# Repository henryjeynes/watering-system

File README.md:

# watering-system

**This project is on hold for the moment. The boards, schematics, and code in this repo are not guaranteed to work. Please let me know if you have any questions about the project.**

Automatic watering system based on ATmegaxx8 microcontrollers.

Using the code or boards is not currently recommended for long-term use.

TODO:
(items in **bold** are scheduled for the next release. Items which have been dealt with are ~~struck through~~.)
  * Add EEPROM-stored settings, which can be changed over the serial port
  * Add sleep code for lower power consumption
  * ~~Add individual watering. The code currently uses one pump for both plants~~
  * Replace linear regulator with switching
  * Add optional float switch for water tank
  * Add optional voltage sensing for batteries (with settings for various chemistries)

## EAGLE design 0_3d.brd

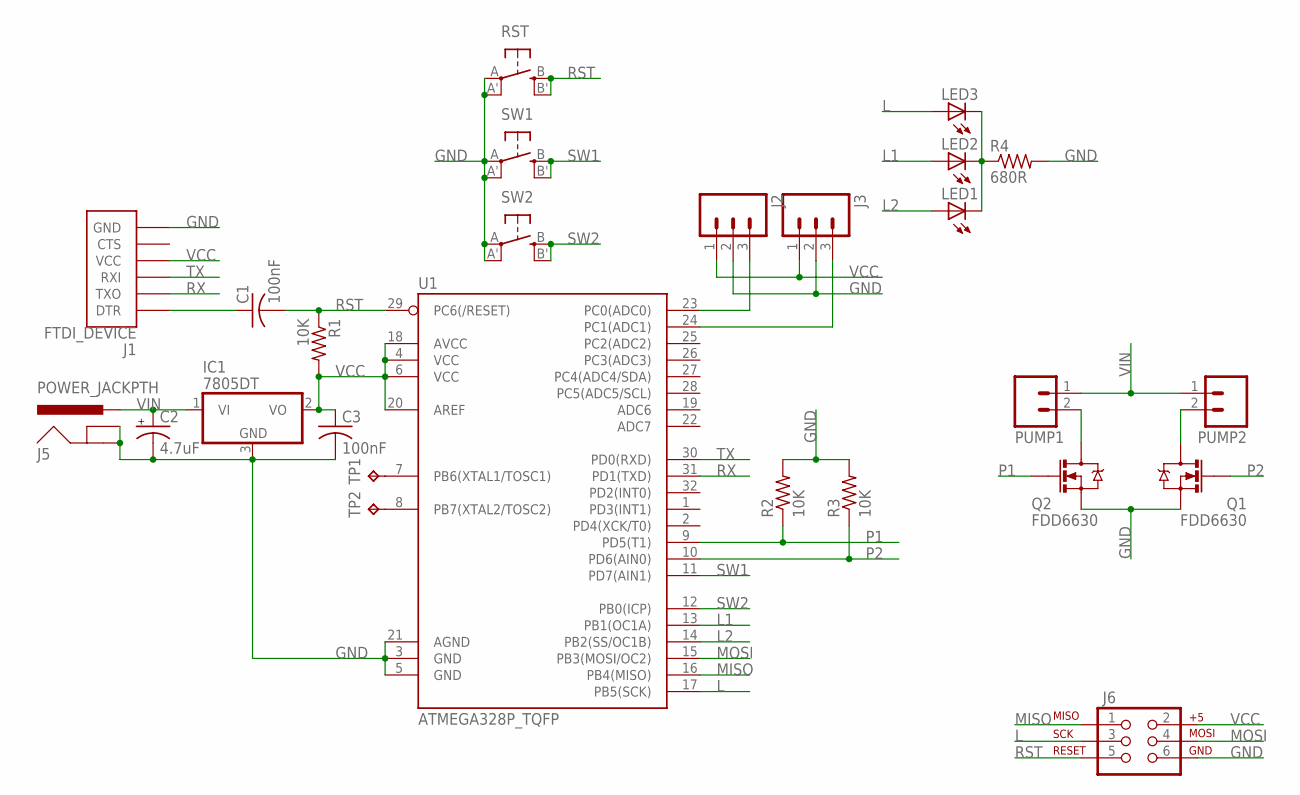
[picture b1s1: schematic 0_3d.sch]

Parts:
C1, C3: 100nF; C1206K
C2: 4.7uF; 153CLV-0405
IC1: 7805DT; TO252
J1: FTDI_DEVICE; FTDI_DEVICE_SIDE
J2, J3: M03PTH; 1X03
J5: POWER_JACKPTH; POWER_JACK_PTH
J6: AVR_SPI_PRG_6PTH; 2X3
LED1, LED2, LED3: LED3MM
PUMP1, PUMP2: M02PTH; 1X02
Q1, Q2: FDD6630; D-PAK_TO252AA
R1, R2, R3: 10K; M0805
R4: 680R; M0805
RST: SPST_TACT-EVQQ2; EVQ-Q2
SW1, SW2: SPST_TACT-EVQQ2; EVQ-Q2
TP1, TP2: TPTP15SQ; TP15SQ
U1: ATMEGA328P_TQFP; TQFP32-08

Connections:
GND: C2.-, C3.2, IC1.3 (GND), J1.P$6 (GND), J2.2, J3.2, J5.GND, J5.GNDBREAK, J6.6, Q1.3 (S), Q2.3 (S), R2.2, R3.2, R4.2, RST.A, RST.A' (P1), SW1.A, SW1.A' (P1), SW2.A, SW2.A' (P1), U1.3 (GND), U1.5 (GND), U1.21 (AGND)
L: J6.3, LED3.A, U1.17 (PB5(SCK))
L1: LED2.A, U1.13 (PB1(OC1A))
L2: LED1.A, U1.14 (PB2(SS/OC1B))
MISO: J6.1, U1.16 (PB4(MISO))
MOSI: J6.4, U1.15 (PB3(MOSI/OC2))
unnamed: LED1.K (C), LED2.K (C), LED3.K (C), R4.1
unnamed: TP1.TP, U1.7 (PB6(XTAL1/TOSC1))
unnamed: PUMP2.2, Q1.2 (D)
unnamed: C1.1, J1.P$1 (DTR)
unnamed: TP2.TP, U1.8 (PB7(XTAL2/TOSC2))
unnamed: PUMP1.2, Q2.2 (D)
unnamed: J2.3, U1.23 (PC0(ADC0))
unnamed: J3.3, U1.24 (PC1(ADC1))
P1: Q2.1 (G), R2.1, U1.9 (PD5(T1))
P2: Q1.1 (G), R3.1, U1.10 (PD6(AIN0))
RST: C1.2, J6.5, R1.1, RST.B (S), RST.B' (S1), U1.29 (PC6(/RESET))
RX: J1.P$2 (TXO), U1.31 (PD1(TXD))
SW1: SW1.B (S), SW1.B' (S1), U1.11 (PD7(AIN1))
SW2: SW2.B (S), SW2.B' (S1), U1.12 (PB0(ICP))
TX: J1.P$3 (RXI), U1.30 (PD0(RXD))
VCC: C3.1, IC1.2 (VO), J1.P$4 (VCC), J2.1, J3.1, J6.2, R1.2, U1.4 (VCC), U1.6 (VCC), U1.18 (AVCC), U1.20 (AREF)
VIN: C2.+, IC1.1 (VI), J5.PWR, PUMP1.1, PUMP2.1

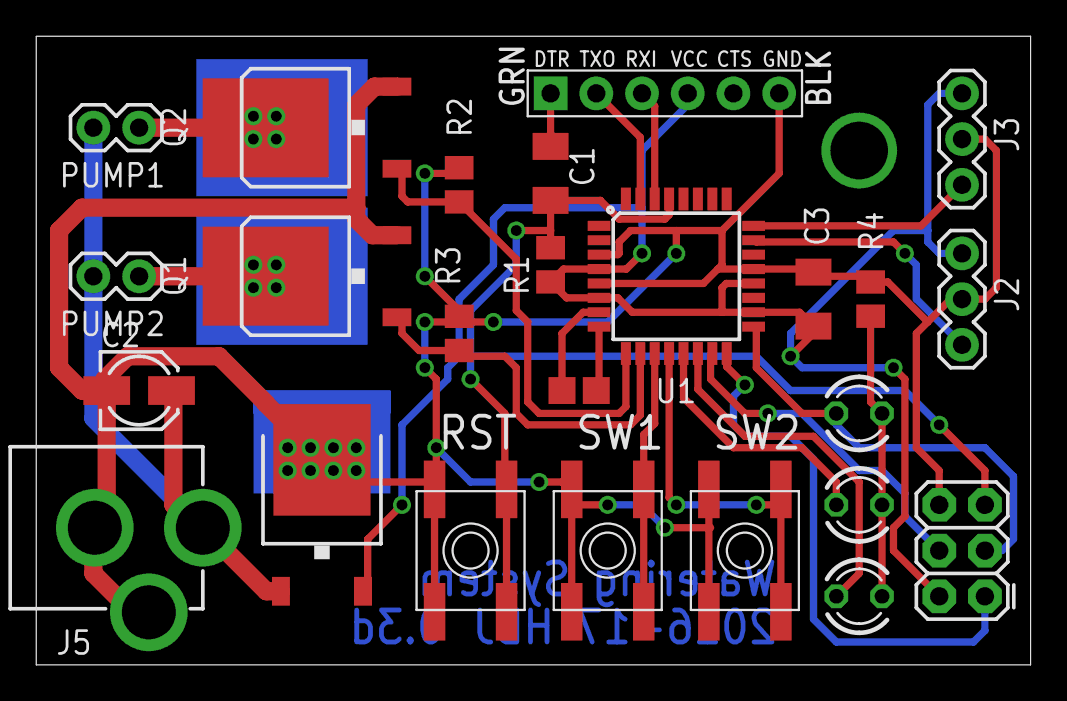
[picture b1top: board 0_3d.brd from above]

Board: 2 copper layers, 55.2 x 34.9 mm, 26 parts (0 on the bottom side), 23 nets.

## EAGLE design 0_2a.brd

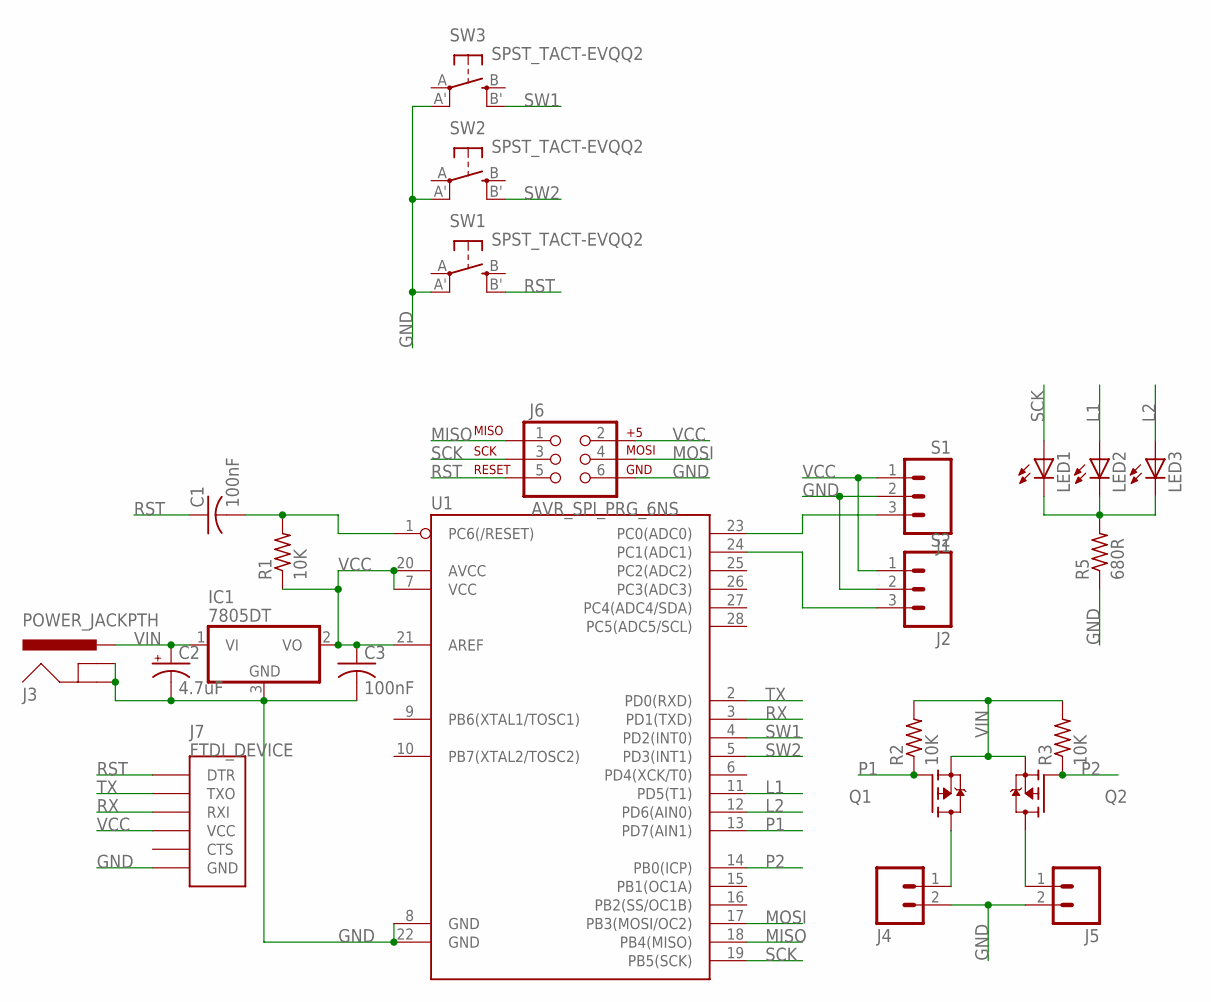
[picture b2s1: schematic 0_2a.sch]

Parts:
C1, C3: 100nF; C1206K
C2: 4.7uF; 153CLV-0405
IC1: 7805DT; TO252
J1: S1; MOLEX-1X3
J2: S2; MOLEX-1X3
J3: POWER_JACKPTH; POWER_JACK_PTH
J4, J5: M02POLAR; MOLEX-1X2
J6: AVR_SPI_PRG_6NS; 2X3-NS
J7: FTDI_DEVICE; FTDI_DEVICE_SIDE
LED1, LED2, LED3: LED3MM
Q1, Q2: FDD4141TO252; TO252
R1, R2, R3: 10K; R0805
R5: 680R; R0805
SW1, SW2, SW3: SPST_TACT-EVQQ2; EVQ-Q2
U1: ATMEGA328P_PDIP; DIL28-3

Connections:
GND: C2.-, C3.2, IC1.3 (GND), J1.2, J2.2, J3.GND, J3.GNDBREAK, J4.2, J5.2, J6.6, J7.P$6 (GND), R5.1, SW1.A' (P1), SW2.A' (P1), SW3.A' (P1), U1.8 (GND), U1.22 (GND)
L1: LED2.A, U1.11 (PD5(T1))
L2: LED3.A, U1.12 (PD6(AIN0))
MISO: J6.1, U1.18 (PB4(MISO))
MOSI: J6.4, U1.17 (PB3(MOSI/OC2))
unnamed: J1.3, U1.23 (PC0(ADC0))
unnamed: J2.3, U1.24 (PC1(ADC1))
unnamed: C1.2, R1.2, U1.1 (PC6(/RESET))
unnamed: J4.1, Q1.3 (D)
unnamed: J5.1, Q2.3 (D)
unnamed: LED1.K (C), LED2.K (C), LED3.K (C), R5.2
P1: Q1.1 (G), R2.1, U1.13 (PD7(AIN1))
P2: Q2.1 (G), R3.1, U1.14 (PB0(ICP))
RST: C1.1, J6.5, J7.P$1 (DTR), SW1.B' (S1)
RX: J7.P$3 (RXI), U1.3 (PD1(TXD))
SCK: J6.3, LED1.A, U1.19 (PB5(SCK))
SW1: SW3.B' (S1), U1.4 (PD2(INT0))
SW2: SW2.B' (S1), U1.5 (PD3(INT1))
TX: J7.P$2 (TXO), U1.2 (PD0(RXD))
VCC: C3.1, IC1.2 (VO), J1.1, J2.1, J6.2, J7.P$4 (VCC), R1.1, U1.7 (VCC), U1.20 (AVCC), U1.21 (AREF)
VIN: C2.+, IC1.1 (VI), J3.PWR, Q1.2 (S), Q2.2 (S), R2.2, R3.2

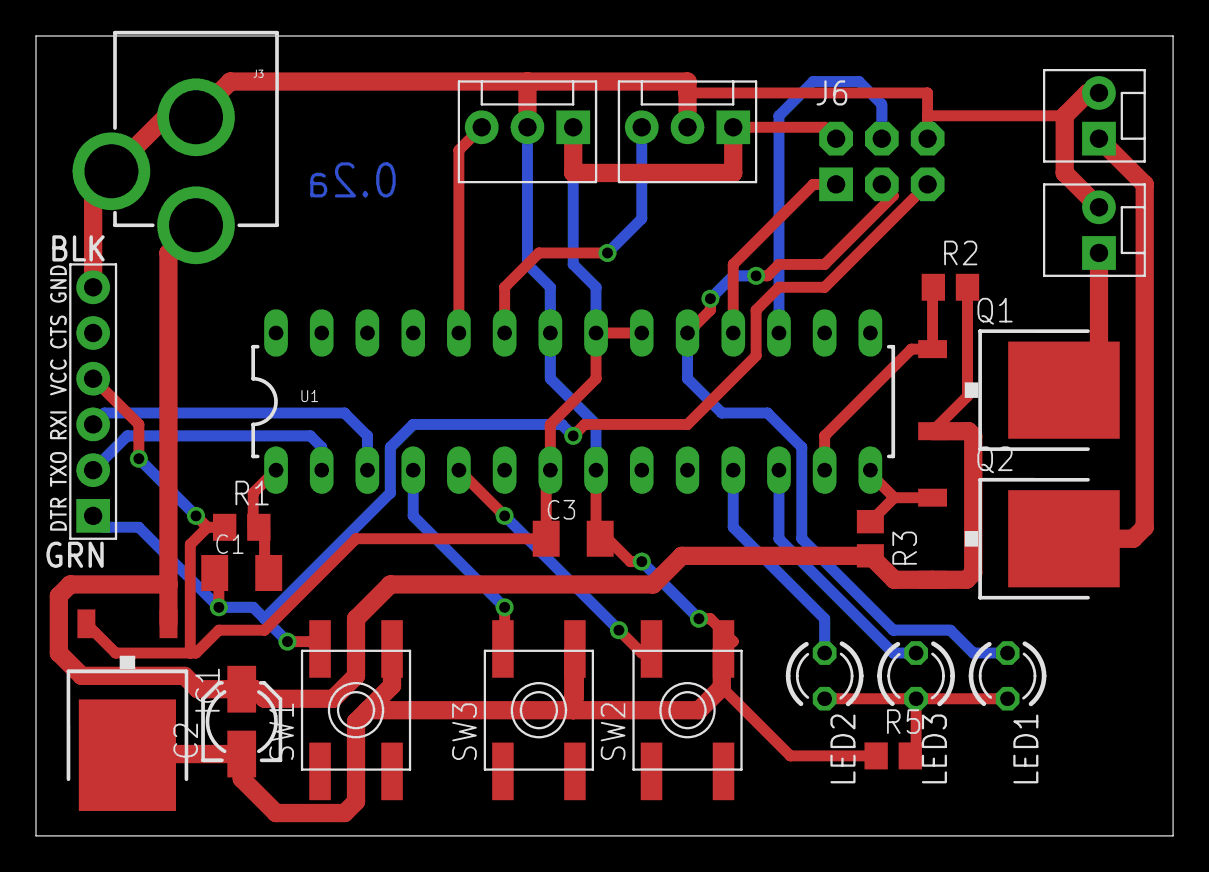
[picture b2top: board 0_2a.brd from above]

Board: 2 copper layers, 63.2 x 44.4 mm, 24 parts (0 on the bottom side), 21 nets.

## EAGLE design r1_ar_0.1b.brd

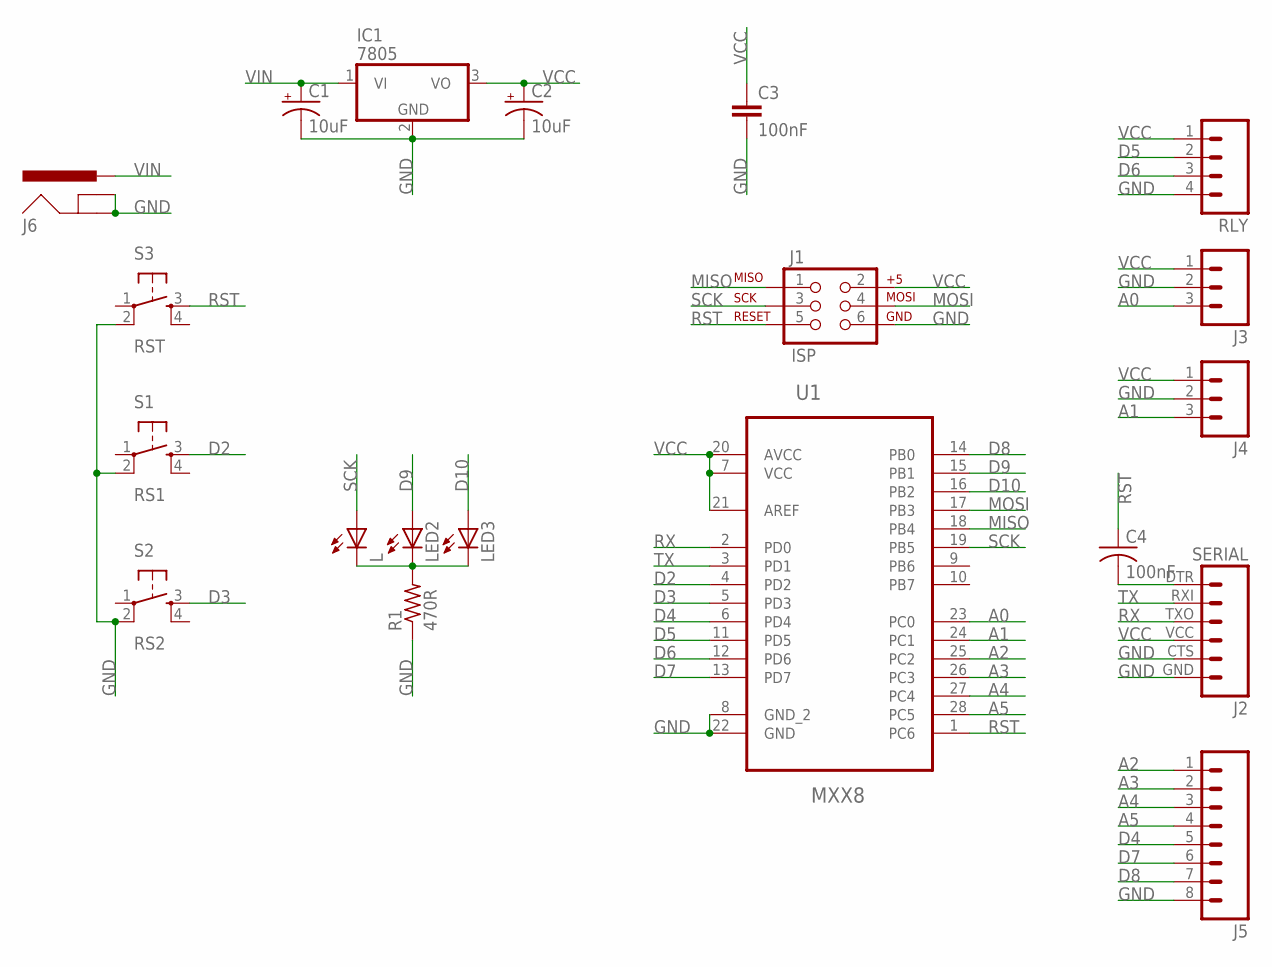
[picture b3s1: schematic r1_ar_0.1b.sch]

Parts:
C1, C2: 10uF; 153CLV-0405
C3: 100nF; CAP-PTH-SMALL
C4: 100nF; C1206K
IC1: 7805; TO220V
J1: ISP; 2X3_LOCK
J2: SERIAL; FTDI_BASIC
J3, J4: M03PTH; 1X03
J5: M08SILK_FEMALE_PTH; 1X08
J6: POWER_JACKSLT; POWER_JACK_SLOT
L: LEDSML0805; SML0805
LED2, LED3: LEDSML0805; SML0805
R1: 470R; M0805
RLY: M04PTH; 1X04
S1: RS1; TACTILE-SWITCH-SMD
S2: RS2; TACTILE-SWITCH-SMD
S3: RST; TACTILE-SWITCH-SMD
U1: MXX8; DIP254P762X457-28

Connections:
A0: J3.3, U1.23 (PC0)
A1: J4.3, U1.24 (PC1)
A2: J5.1, U1.25 (PC2)
A3: J5.2, U1.26 (PC3)
A4: J5.3, U1.27 (PC4)
A5: J5.4, U1.28 (PC5)
D2: S1.3, U1.4 (PD2)
D3: S2.3, U1.5 (PD3)
D4: J5.5, U1.6 (PD4)
D5: RLY.2, U1.11 (PD5)
D6: RLY.3, U1.12 (PD6)
D7: J5.6, U1.13 (PD7)
D8: J5.7, U1.14 (PB0)
D9: LED2.A, U1.15 (PB1)
D10: LED3.A, U1.16 (PB2)
GND: C1.-, C2.-, C3.2, IC1.2 (GND), J1.6, J2.CTS (5), J2.GND (6), J3.2, J4.2, J5.8, J6.GND@1 (GNDBREAK), J6.GND@2 (GND), R1.1, RLY.4, S1.2, S2.2, S3.2, U1.8 (GND_2), U1.22 (GND)
MISO: J1.1, U1.18 (PB4)
MOSI: J1.4, U1.17 (PB3)
unnamed: L.C, LED2.C, LED3.C, R1.2
unnamed: C4.2, J2.DTR (1)
RST: C4.1, J1.5, S3.3, U1.1 (PC6)
RX: J2.TXO (3), U1.2 (PD0)
SCK: J1.3, L.A, U1.19 (PB5)
TX: J2.RXI (2), U1.3 (PD1)
VCC: C2.+, C3.1, IC1.3 (VO), J1.2, J2.VCC (4), J3.1, J4.1, RLY.1, U1.7 (VCC), U1.20 (AVCC), U1.21 (AREF)
VIN: C1.+, IC1.1 (VI), J6.PWR

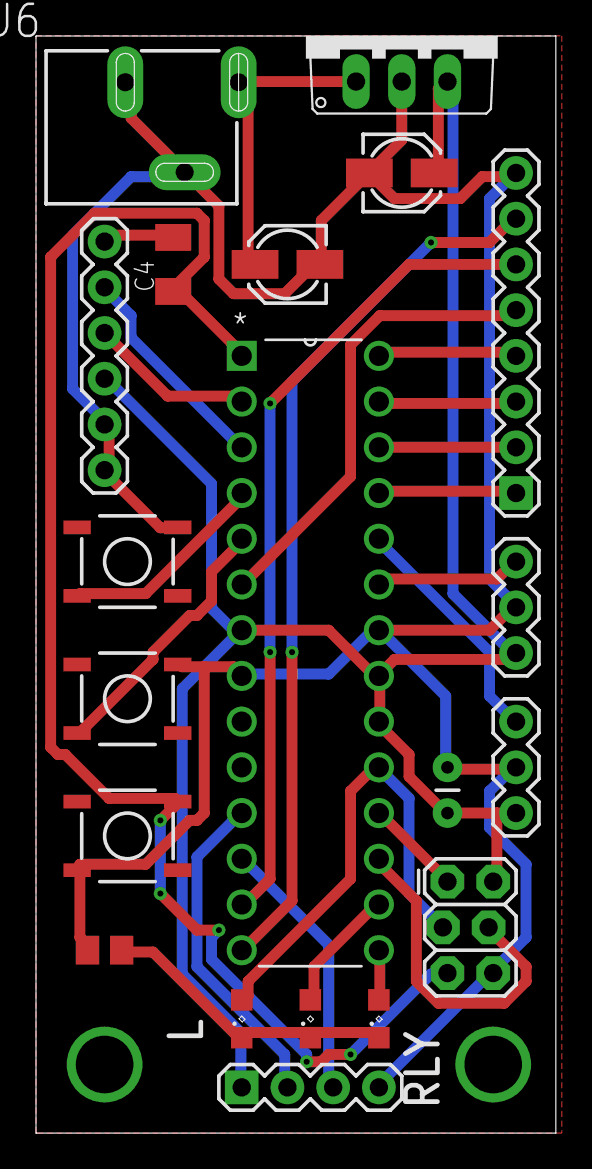
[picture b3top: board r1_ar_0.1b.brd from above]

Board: 2 copper layers, 28.9 x 61.0 mm, 20 parts (0 on the bottom side), 26 nets.

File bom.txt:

bom.txt

C1, C2: 2x 0405 electrolytic capacitors, >= 16v and >= 10uF
C3: 1x 100nF capacitor, through-hole
C4: 1x 100nF capacitor, 1206
IC1: 1x 7805, TO-220
J2: 1x 2x3 2.54mm PTH header
J1: 1x 1x6 2.54mm PTH header
J3, J4: 2x 1x3 2.54mm PTH header
J5: 1x 1x8 2.54mm PTH header
J6: 1x 2.1mm barrel jack
RLY: 1x 1x4 2.54mm header
LED1, LED2, LED3: 3x 0805 LED, any color
RS1, RS2, RST: 3x SMD tactile switches, 5mm
U1: 1x ATmega88PU/168PU/328PU with 28-pin socket

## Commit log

2016-11-05 Added EAGLE files for Hydro 0.1b
    Hydro 0.1b adds the power jack which was missing in the unreleased 0.1a.
2016-11-05 Added Arduino files, version 0.1a
    These Arduino files are designed for the Hydro 0.1b. This version of the program is only intended for testing I/O, such as relays, LEDs, buttons, etc. This version should not be used for watering pla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
2016-11-05 Updated README.md
    Added warning about the incompleteness of the code and boards
2016-11-05 Create version-history
2016-11-05 New version, 0.1b2
    Minor update to 0.1b, mostly shorter idle blink for slightly lower power consumption
2016-11-05 Update version-history
2016-11-05 added BOM
2016-12-24 Update version-history
    Added 0.1c, not released yet
2016-12-24 Update version-history
    more details about 0.1c
2017-01-05 Uploaded Hydro 0.2a
2017-01-24 Added board version 0.3b
    Refer to version-history.txt for more info
2017-01-24 Update README.md
    Removed the line about adding MOSFETs. Version 0.3b now has built-in switching
2017-02-04 Added 0.3c
    0.2b had a minor design flaw which rendered the whole board useless.
2017-02-04 Rename 0_3cbrd.brd to 0_3c.brd
2017-02-27 Added board version 0.3d
2017-06-12 Edit README.md
    Due to some trouble with the code, EEPROM-stored settings will be released after the next version.
2017-06-12 Added board version 0.4b
    Current revision of 0.4b, may be changed later. Untested

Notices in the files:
parts and their libraries:
SparkFun-Connectors: Licensing: Creative Commons ShareAlike 4.0 International - https://creativecommons.org/licenses/by-sa/4.0
